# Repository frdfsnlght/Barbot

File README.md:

# Barbot
My Barbot project

This repository stores all the design artifacts for the project and is freely
available to anyone who wants to learn about my project.

## Why?

There are hundreds, if not thousands, of barbots made by makers all over the world.
It might be a right of passage for some, but for me, it was an interesting idea that
gave me an excuse to learn some new things.

I had the idea to build one of these things years ago with a friend. The main detraction
for me was that most barbot build I've seen are either too large or too slow, in my
opinion. If I was going to build one of these, it had to be small and convenient
enough to easily store when not in use, easy to clean after being used, and it couldn't
take forever to dispense a drink.
Those requirements are completely subjective but I eventually came up
with some numbers that would satisfy me. My goals were to be able to store the device
on an existing shelf in a spare room in my house and it had to be able to make me a
drink (e.g., a rum and coke) in under 10 seconds. The cleaning aspect is more difficult
to quantify but I didn't want to have to disassemble the device or do anything else
drastic to get it cleaned up.

## How?

In the spring of 2018 I revisited the idea of building a barbot when I found some
published builds using peristaltic pumps. I had never considered individual pumps
for each ingredient, but doing so solved some of the problems I felt other designs
suffered from. After investigating, I discovered peristaltic pumps generally come
in two forms, small and slow, or large and expensive. Neither was satisfactory, so
I started  considering making my own pumps. This eventually led to 3D printing,
something I had never really had a need of before. I started designing a
pump that could meet my needs and eventually bought a 3D printer and started
building a prototype. After a few iterations and lots of fiddling around, I came
up with a design that worked. You can find out more about the pump [here](3D).

Once I had the pump designed and tested, the possibility of building a complete
barbot became real. All I would need to do was the rest of the design and build.

## More to come...

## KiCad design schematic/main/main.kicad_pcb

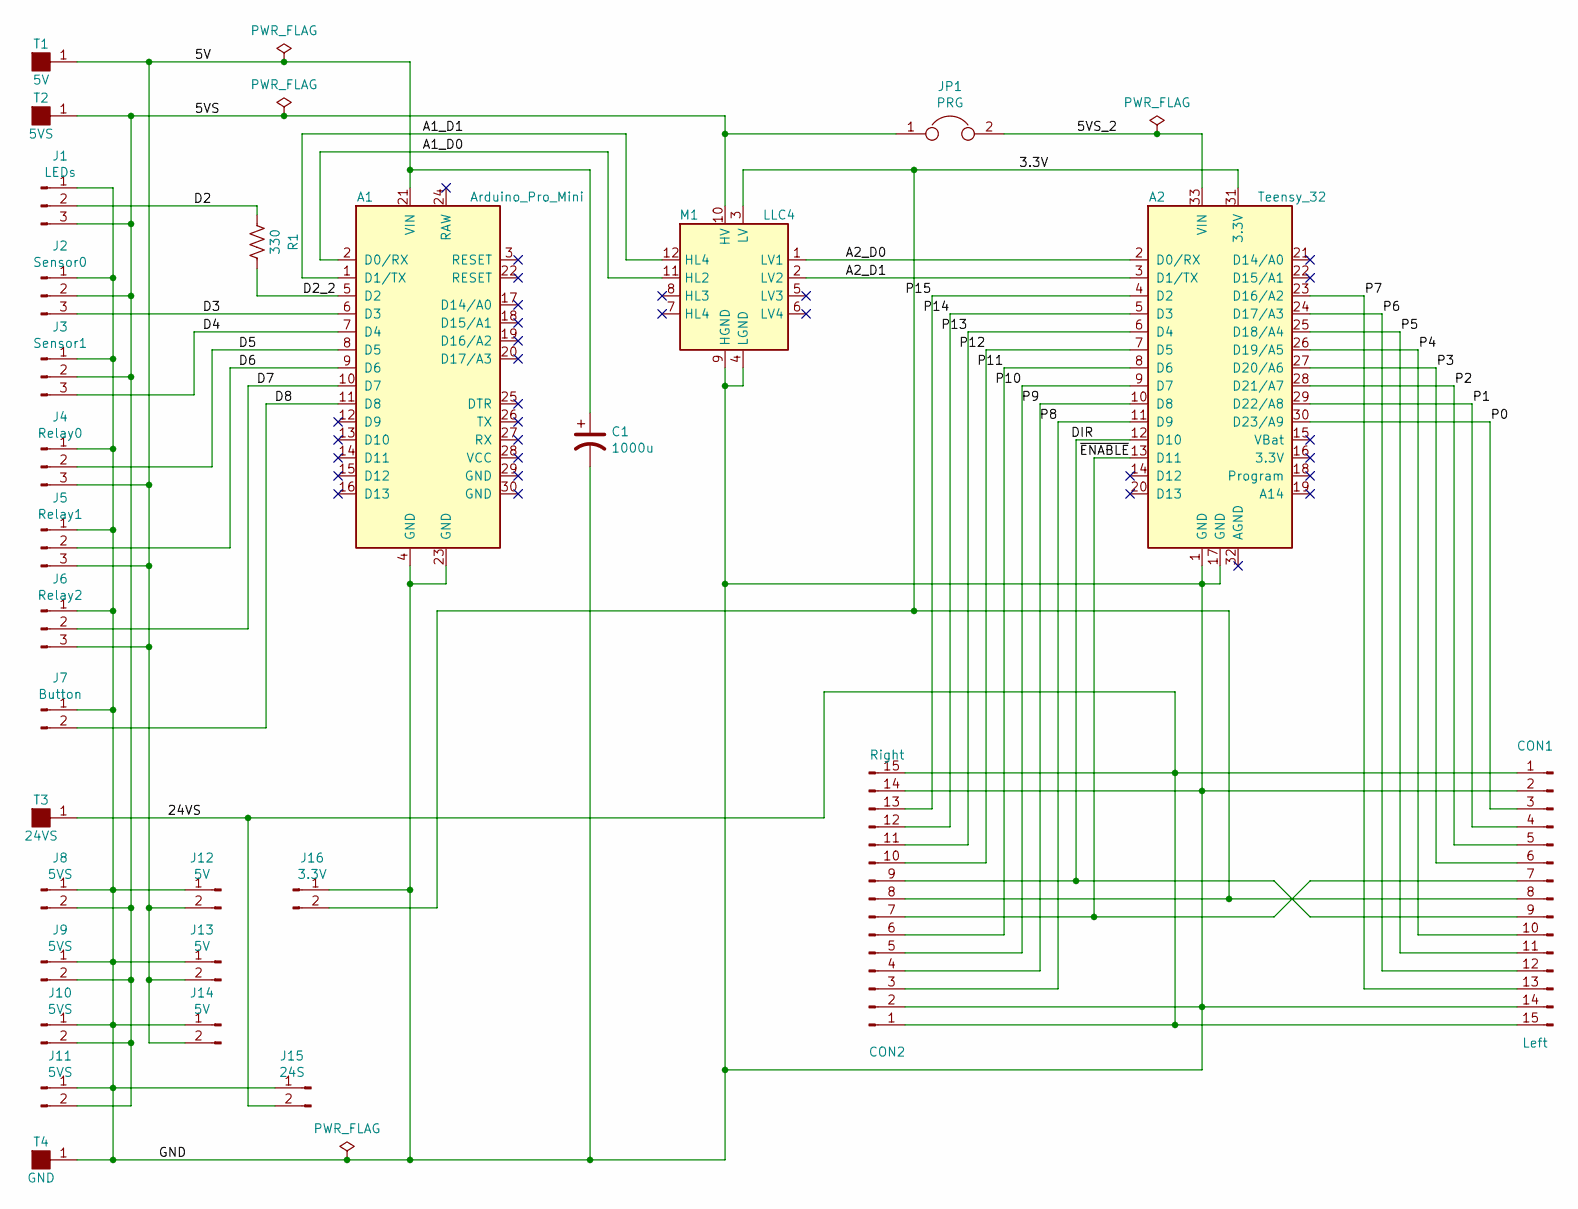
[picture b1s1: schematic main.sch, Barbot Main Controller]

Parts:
A1: Arduino_Pro_Mini; arduino_pro_mini
A2: Teensy_32; teensy_32
C1: 1000u; CP_Radial_D10.0mm_P5.00mm
CON1: Left; Pin_Header_Angled_1x15_Pitch2.54mm
CON2: Right; Pin_Header_Angled_1x15_Pitch2.54mm
J1: LEDs; Pin_Header_Straight_1x03_Pitch2.54mm
J2: Sensor0; Pin_Header_Straight_1x03_Pitch2.54mm
J3: Sensor1; Pin_Header_Straight_1x03_Pitch2.54mm
J4: Relay0; Pin_Header_Straight_1x03_Pitch2.54mm
J5: Relay1; Pin_Header_Straight_1x03_Pitch2.54mm
J6: Relay2; Pin_Header_Straight_1x03_Pitch2.54mm
J7: Button; Pin_Header_Straight_1x02_Pitch2.54mm
J8, J9, J10, J11: 5VS; Pin_Header_Straight_1x02_Pitch2.54mm
J12, J13, J14: 5V; Pin_Header_Straight_1x02_Pitch2.54mm
J15: 24S; Pin_Header_Straight_1x02_Pitch2.54mm
J16: 3.3V; Pin_Header_Straight_1x02_Pitch2.54mm
JP1: PRG; Pin_Header_Straight_1x02_Pitch2.54mm
M1: LLC4
R1: 330; R_Axial_DIN0207_L6.3mm_D2.5mm_P2.54mm_Vertical
T1: 5V; Spade_Terminal_1_4
T2: 5VS; Spade_Terminal_1_4
T3: 24VS; Spade_Terminal_1_4
T4: GND; Spade_Terminal_1_4

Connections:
/3.3V: A2.31 (3.3V), CON1.8, CON2.8, J16.2, M1.3 (LV)
/5V: A1.21 (VIN), C1.1, J4.3, J5.3, J6.3, J12.2, J13.2, J14.2, T1.1
/5VS: J1.3, J2.2, J3.2, J8.2, J9.2, J10.2, J11.2, JP1.1, M1.10 (HV), T2.1
/5VS_2: A2.33 (VIN), JP1.2
/24VS: CON1.1, CON1.15, CON2.1, CON2.15, J15.2, T3.1
/A1_D0: A1.2 (D0/RX), M1.11 (HL2)
/A1_D1: A1.1 (D1/TX), M1.12 (HL4)
/A2_D0: A2.2 (D0/RX), M1.1 (LV1)
/A2_D1: A2.3 (D1/TX), M1.2 (LV2)
/D2: J1.2, R1.1
/D2_2: A1.5 (D2), R1.2
/D3: A1.6 (D3), J2.3
/D4: A1.7 (D4), J3.3
/D5: A1.8 (D5), J4.2
/D6: A1.9 (D6), J5.2
/D7: A1.10 (D7), J6.2
/D8: A1.11 (D8), J7.2
/DIR: A2.12 (D10), CON1.9, CON2.9
/GND: A1.4 (GND), A1.23 (GND), A2.1 (GND), A2.17 (GND), C1.2, CON1.2, CON1.14, CON2.2, CON2.14, J1.1, J2.1, J3.1, J4.1, J5.1, J6.1, J7.1, J8.1, J9.1, J10.1, J11.1, J12.1, J13.1, J14.1, J15.1, J16.1, M1.4 (LGND), M1.9 (HGND), T4.1
/P0: A2.30 (D23/A9), CON1.3
/P1: A2.29 (D22/A8), CON1.4
/P2: A2.28 (D21/A7), CON1.5
/P3: A2.27 (D20/A6), CON1.6
/P4: A2.26 (D19/A5), CON1.10
/P5: A2.25 (D18/A4), CON1.11
/P6: A2.24 (D17/A3), CON1.12
/P7: A2.23 (D16/A2), CON1.13
/P8: A2.11 (D9), CON2.3
/P9: A2.10 (D8), CON2.4
/P10: A2.9 (D7), CON2.5
/P11: A2.8 (D6), CON2.6
/P12: A2.7 (D5), CON2.10
/P13: A2.6 (D4), CON2.11
/P14: A2.5 (D3), CON2.12
/P15: A2.4 (D2), CON2.13
/~ENABLE: A2.13 (D11), CON1.7, CON2.7

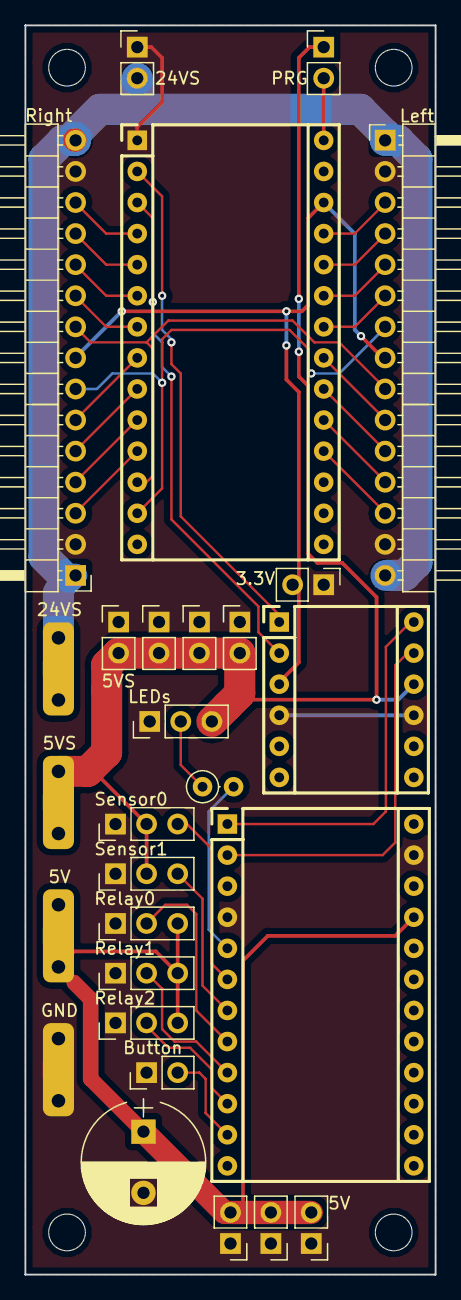
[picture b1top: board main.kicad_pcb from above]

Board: 2 copper layers, 33.5 x 102.1 mm, 28 parts (0 on the bottom side), 36 nets.

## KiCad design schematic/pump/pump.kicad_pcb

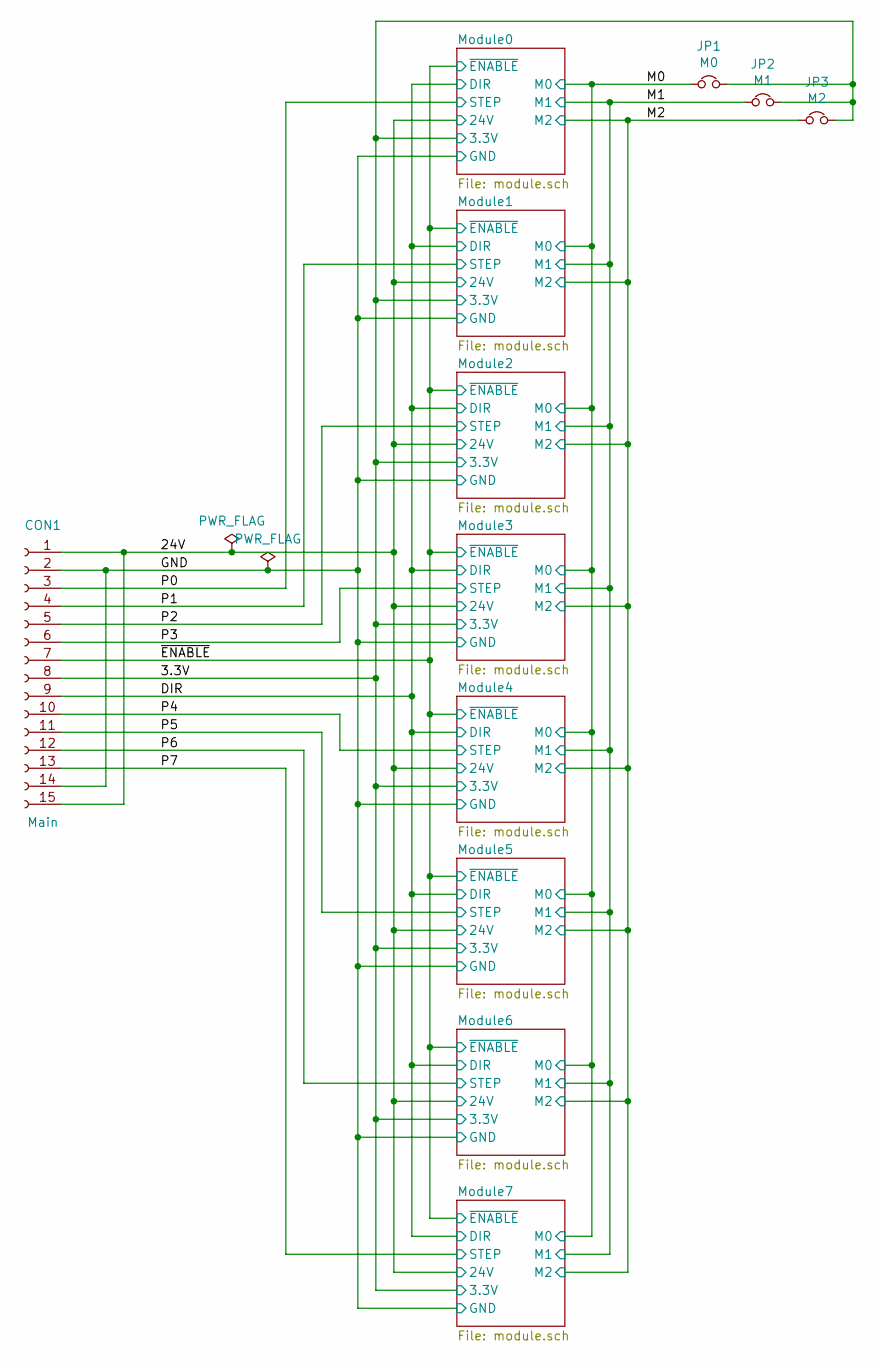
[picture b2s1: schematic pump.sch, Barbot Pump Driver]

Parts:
CON1: Main; Socket_Strip_Angled_1x15_Pitch2.54mm
JP1: M0; Pin_Header_Straight_2x01_Pitch2.54mm
JP2: M1; Pin_Header_Straight_2x01_Pitch2.54mm
JP3: M2; Pin_Header_Straight_2x01_Pitch2.54mm

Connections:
/3.3V: CON1.8, JP1.2, JP2.2, JP3.2; also elsewhere on the board
/24V: CON1.1, CON1.15; also elsewhere on the board
/DIR: CON1.9; also elsewhere on the board
/GND: CON1.2, CON1.14; also elsewhere on the board
/M0: JP1.1; also elsewhere on the board
/M1: JP2.1; also elsewhere on the board
/M2: JP3.1; also elsewhere on the board
/P0: CON1.3; also elsewhere on the board
/P1: CON1.4; also elsewhere on the board
/P2: CON1.5; also elsewhere on the board
/P3: CON1.6; also elsewhere on the board
/P4: CON1.10; also elsewhere on the board
/P5: CON1.11; also elsewhere on the board
/P6: CON1.12; also elsewhere on the board
/P7: CON1.13; also elsewhere on the board
/~ENABLE: CON1.7; also elsewhere on the board

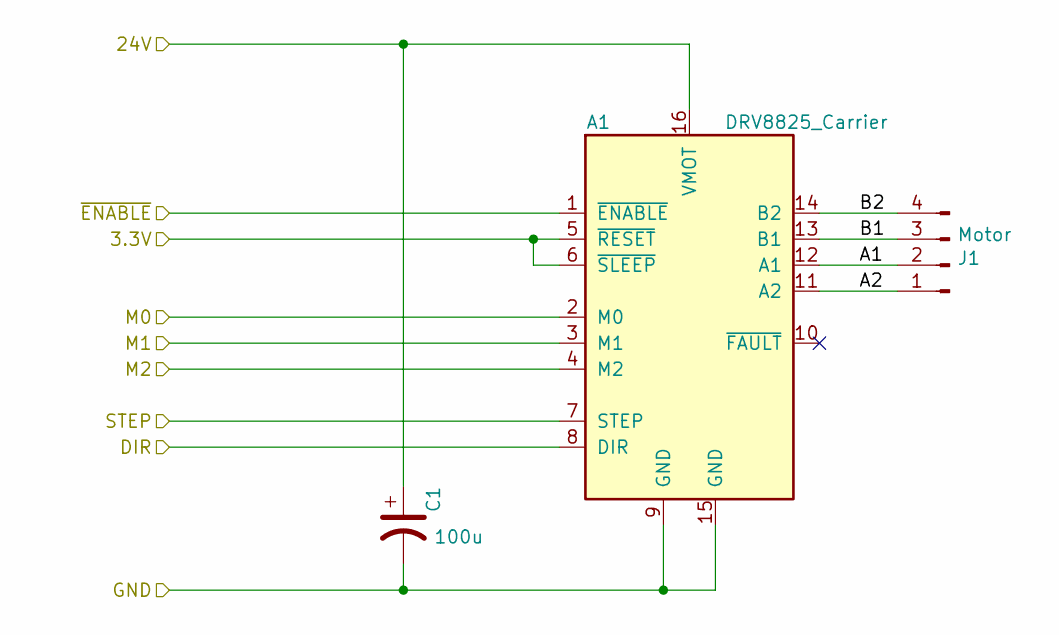
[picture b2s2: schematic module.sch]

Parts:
A1: DRV8825_Carrier; Pololu_Breakout-16_15.2x20.3mm
C1: 100u; CP_Radial_D6.3mm_P2.50mm
J1: Motor; Pin_Header_Straight_1x04_Pitch2.54mm

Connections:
/3.3V: A1.5 (~RESET), A1.6 (~SLEEP); also elsewhere on the board
/24V: A1.16 (VMOT), C1.1; also elsewhere on the board
/DIR: A1.8 (DIR); also elsewhere on the board
/GND: A1.9 (GND), A1.15 (GND), C1.2; also elsewhere on the board
/M0: A1.2 (M0); also elsewhere on the board
/M1: A1.3 (M1); also elsewhere on the board
/M2: A1.4 (M2); also elsewhere on the board
/Module1/A1: A1.12 (A1), J1.2
/Module1/A2: A1.11 (A2), J1.1
/Module1/B1: A1.13 (B1), J1.3
/Module1/B2: A1.14 (B2), J1.4
/P1: A1.7 (STEP); also elsewhere on the board
/~ENABLE: A1.1 (~ENABLE); also elsewhere on the board

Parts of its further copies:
A0, A2, A3, A4, A5, A6, A7: DRV8825_Carrier; Pololu_Breakout-16_15.2x20.3mm
C0, C2, C3, C4, C5, C6, C7: 100u; CP_Radial_D6.3mm_P2.50mm
J0, J2, J3, J4, J5, J6, J7: Motor; Pin_Header_Straight_1x04_Pitch2.54mm

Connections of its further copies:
/3.3V: A0.5 (~RESET), A0.6 (~SLEEP), A2.5 (~RESET), A2.6 (~SLEEP), A3.5 (~RESET), A3.6 (~SLEEP), A4.5 (~RESET), A4.6 (~SLEEP), A5.5 (~RESET), A5.6 (~SLEEP), A6.5 (~RESET), A6.6 (~SLEEP), A7.5 (~RESET), A7.6 (~SLEEP); also elsewhere on the board
/24V: A0.16 (VMOT), A2.16 (VMOT), A3.16 (VMOT), A4.16 (VMOT), A5.16 (VMOT), A6.16 (VMOT), A7.16 (VMOT), C0.1, C2.1, C3.1, C4.1, C5.1, C6.1, C7.1; also elsewhere on the board
/DIR: A0.8 (DIR), A2.8 (DIR), A3.8 (DIR), A4.8 (DIR), A5.8 (DIR), A6.8 (DIR), A7.8 (DIR); also elsewhere on the board
/GND: A0.9 (GND), A0.15 (GND), A2.9 (GND), A2.15 (GND), A3.9 (GND), A3.15 (GND), A4.9 (GND), A4.15 (GND), A5.9 (GND), A5.15 (GND), A6.9 (GND), A6.15 (GND), A7.9 (GND), A7.15 (GND), C0.2, C2.2, C3.2, C4.2, C5.2, C6.2, C7.2; also elsewhere on the board
/M0: A0.2 (M0), A2.2 (M0), A3.2 (M0), A4.2 (M0), A5.2 (M0), A6.2 (M0), A7.2 (M0); also elsewhere on the board
/M1: A0.3 (M1), A2.3 (M1), A3.3 (M1), A4.3 (M1), A5.3 (M1), A6.3 (M1), A7.3 (M1); also elsewhere on the board
/M2: A0.4 (M2), A2.4 (M2), A3.4 (M2), A4.4 (M2), A5.4 (M2), A6.4 (M2), A7.4 (M2); also elsewhere on the board
/Module0/A1: A0.12 (A1), J0.2
/Module0/A2: A0.11 (A2), J0.1
/Module0/B1: A0.13 (B1), J0.3
/Module0/B2: A0.14 (B2), J0.4
/Module2/A1: A2.12 (A1), J2.2
/Module2/A2: A2.11 (A2), J2.1
/Module2/B1: A2.13 (B1), J2.3
/Module2/B2: A2.14 (B2), J2.4
/Module3/A1: A3.12 (A1), J3.2
/Module3/A2: A3.11 (A2), J3.1
/Module3/B1: A3.13 (B1), J3.3
/Module3/B2: A3.14 (B2), J3.4
/Module4/A1: A4.12 (A1), J4.2
/Module4/A2: A4.11 (A2), J4.1
/Module4/B1: A4.13 (B1), J4.3
/Module4/B2: A4.14 (B2), J4.4
/Module5/A1: A5.12 (A1), J5.2
/Module5/A2: A5.11 (A2), J5.1
/Module5/B1: A5.13 (B1), J5.3
/Module5/B2: A5.14 (B2), J5.4
/Module6/A1: A6.12 (A1), J6.2
/Module6/A2: A6.11 (A2), J6.1
/Module6/B1: A6.13 (B1), J6.3
/Module6/B2: A6.14 (B2), J6.4
/Module7/A1: A7.12 (A1), J7.2
/Module7/A2: A7.11 (A2), J7.1
/Module7/B1: A7.13 (B1), J7.3
/Module7/B2: A7.14 (B2), J7.4
/P0: A0.7 (STEP); also elsewhere on the board
/P2: A2.7 (STEP); also elsewhere on the board
/P3: A3.7 (STEP); also elsewhere on the board
/P4: A4.7 (STEP); also elsewhere on the board
/P5: A5.7 (STEP); also elsewhere on the board
/P6: A6.7 (STEP); also elsewhere on the board
/P7: A7.7 (STEP); also elsewhere on the board
/~ENABLE: A0.1 (~ENABLE), A2.1 (~ENABLE), A3.1 (~ENABLE), A4.1 (~ENABLE), A5.1 (~ENABLE), A6.1 (~ENABLE), A7.1 (~ENABLE); also elsewhere on the board

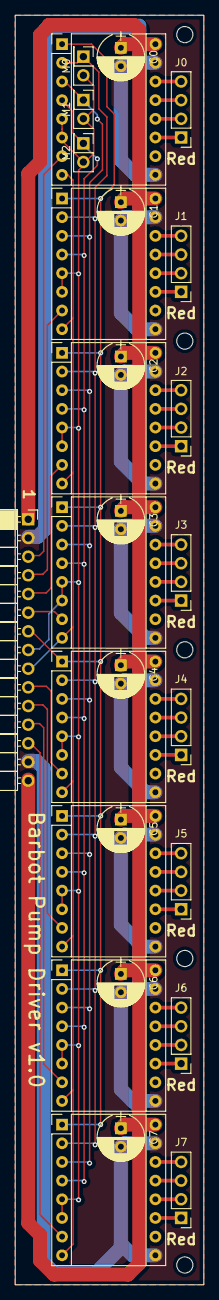
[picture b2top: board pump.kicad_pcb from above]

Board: 2 copper layers, 25.7 x 172.7 mm, 28 parts (0 on the bottom side), 48 nets.

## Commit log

2018-10-22 Initial commit of merged repository.
2018-10-23 Added schematics and 3D directories
2018-10-24 PCBs started!
2018-10-25 Tuning and bug fixing.
2018-10-25 Changed pin assignments
2018-10-25 Fixed sensor sense
2018-10-26 Fixed wifi issues
2018-10-26 Various fixes
2018-10-26 Added shutdownTimer
2018-10-26 Fixed bad thrown exception
2018-10-26 Fixed config references
2018-10-26 Finished board designs.
2018-10-26 Fixed restart and shutdown process.
2018-10-26 Added controller
2018-10-27 Tweak relay delay, added light pattern debugging
2018-10-29 Tweaked schematic and board
2018-10-29 Tweaked sun gears and roller for standard stepper
2018-10-29 More detail
2018-10-30 Tweaked some pads
2018-10-31 Small tweaks
2018-10-31 Lots more work done
2018-11-01 Debugging
2018-11-01 Ignore existing PID file on startup.
2018-11-01 Tweaking serial speed
2018-11-01 Added nut recess to dispenser head.
2018-11-01 Added STLs and print settings
2018-11-02 More printing
2018-11-02 More STLs
2018-11-02 Better serial command handling
2018-11-02 Client side alert support
2018-11-02 Started virtual keyboard
2018-11-06 Virtual keyboard integrated
2018-11-06 BOM and added panel
2018-11-06 Timings/progress
2018-11-07 Tweaked keyboard
2018-11-07 Started new audio engine
2018-11-08 Fixed audio effects bug
2018-11-08 New controller box
2018-11-09 New speakers and controller enclosure
2018-11-09 More controller design
2018-11-09 DB updates, audio fixes, volume control fixes, better daemon support
2018-11-13 Dimensioning for fabrication
2018-11-13 Reformatted BOM
2018-11-13 More reformatting
2018-11-13 More
2018-11-13 More changes
2018-11-13 New STL
2018-11-13 New grill
2018-11-13 New design
2018-11-13 More STLs and 3D tuning
2018-11-13 Added pump flushing
2018-11-14 URL tweaks
2018-11-14 More URL tweaks
2018-11-14 Testing
2018-11-14 Test
2018-11-14 Updated URLs
2018-11-14 Refactored pump setup
2018-11-14 Added eventlet monkey patching, again.
2018-11-14 More STLs and enclosure tweaks
2018-11-14 Updated TODO
2018-11-19 Added serial CRC.
2018-11-19 Added CRC
2018-11-20 Tweaks, new dispenser head part B
2018-11-20 Cleaned up bin directory and added more tools.
2018-11-20 Added some color to empty icon
2018-11-20 Added some documentation.
2018-11-20 Redesigned dispenser tubing
2018-11-21 Added baseline glasses, ingredients, and drinks.
2018-11-21 Made importing ingredients and drinks more forgiving.
2018-11-21 Tweaked
2018-11-21 Small changes
2018-11-26 Debugged some new stuff
2018-11-26 No real changes
2018-11-26 Added reload and restart X commands
2018-11-26 Refactor and MakeMyOwn added
2018-11-26 Added position output on motor stop
2018-11-27 Bug fixes, some icons, cleanup
2018-11-27 Check flushing before some operations
2018-11-28 Added simulated power button
2018-11-28 Finished Make My Own, componentized shit, bug fixes, more refactoring, etc.
2018-11-29 Tweaks
2018-11-29 Forget to return a config value to default
2018-11-29 Fixed restartX command
2018-11-29 Fixed checksum and socket bugs
2018-11-29 Added configurable delay for restart and shutdown
2018-11-30 Hopefully fixed comms between controllers
2018-11-30 Set pump speed/accel on start
2018-12-01 Changed
2018-12-02 Changed primeFactor
2018-12-03 Fixed spelling of lemomade, uh, I mean lemonade
2018-12-03 Replaced utils with more configurable units
2018-12-03 Fixed some units things
2018-12-03 Cleanup
2018-12-03 Added var/glass
2018-12-03 Ingredients remember last container size, unused amount and units
2018-12-04 Huge refactor, not quite done yet
2018-12-05 More refactoring
2018-12-07 Done refactoring, added settings
2018-12-07 Can now clear ingredients
2018-12-10 Added alternative ingredients
2018-12-11 Finished ingredient alternatives
2018-12-12 Added About screen, fixed scrollbars, cleaned up dialogs and events
2018-12-12 Removed virtual keyboard from select elements
2018-12-12 Fixed bad event name
2018-12-12 Added basic support for fractional amounts
2018-12-12 Added teaspoon and tablespoon units
2018-12-12 Cleaned up TODO
2018-12-12 Added build date
2018-12-14 Added basic statistics
2018-12-14 Added compact export/import
2018-12-14 Fixed a couple of bugs
2018-12-14 More drinks and ingredients!
2018-12-14 Added 'back' to the drawer, moved About up
2018-12-16 Removed virtual keyboard from glass drop-down
2018-12-16 Added diskFree to statistics
2018-12-16 Added pumpEmpty audio clip
2018-12-16 Fixed startPump
2018-12-16 Fixed continuous rotation forward/reverse
2018-12-16 Fixed scrollbars
2018-12-16 Strip hostname and addresses
2018-12-16 Fixed bugs
2018-12-16 Added vi swap files
2018-12-16 Better pump values and playing with lights
2018-12-16 Removed old code
2018-12-16 Fixed state transition for unloading pump
2018-12-16 Disabled some light patterns until power down issue is resolved
2018-12-16 Fixed stupid typos
2018-12-16 Small cleanup
2018-12-26 Replaced dynamic allocations with static, removed unused light patterns, renumbered existing patterns
2018-12-26 Removed dynamic memory DEallocations! D'oh!
2018-12-28 Increased number of allowed multiwipe colors
2018-12-28 Fixed bus event name
2018-12-28 Fixed state transition to same state
2018-12-28 Added idle light pattern, reenabled disabled patterns for testing
2018-12-28 Removed unused code
2018-12-29 Removed lights off on power up
2018-12-29 Added idle pattern on loop start
2018-12-30 Tweaked startup lights
2018-12-30 Fixed idle pattern
2018-12-30 Fixed rounding
2018-12-30 Fixed drain bug
2019-01-04 Fixed bad response key
